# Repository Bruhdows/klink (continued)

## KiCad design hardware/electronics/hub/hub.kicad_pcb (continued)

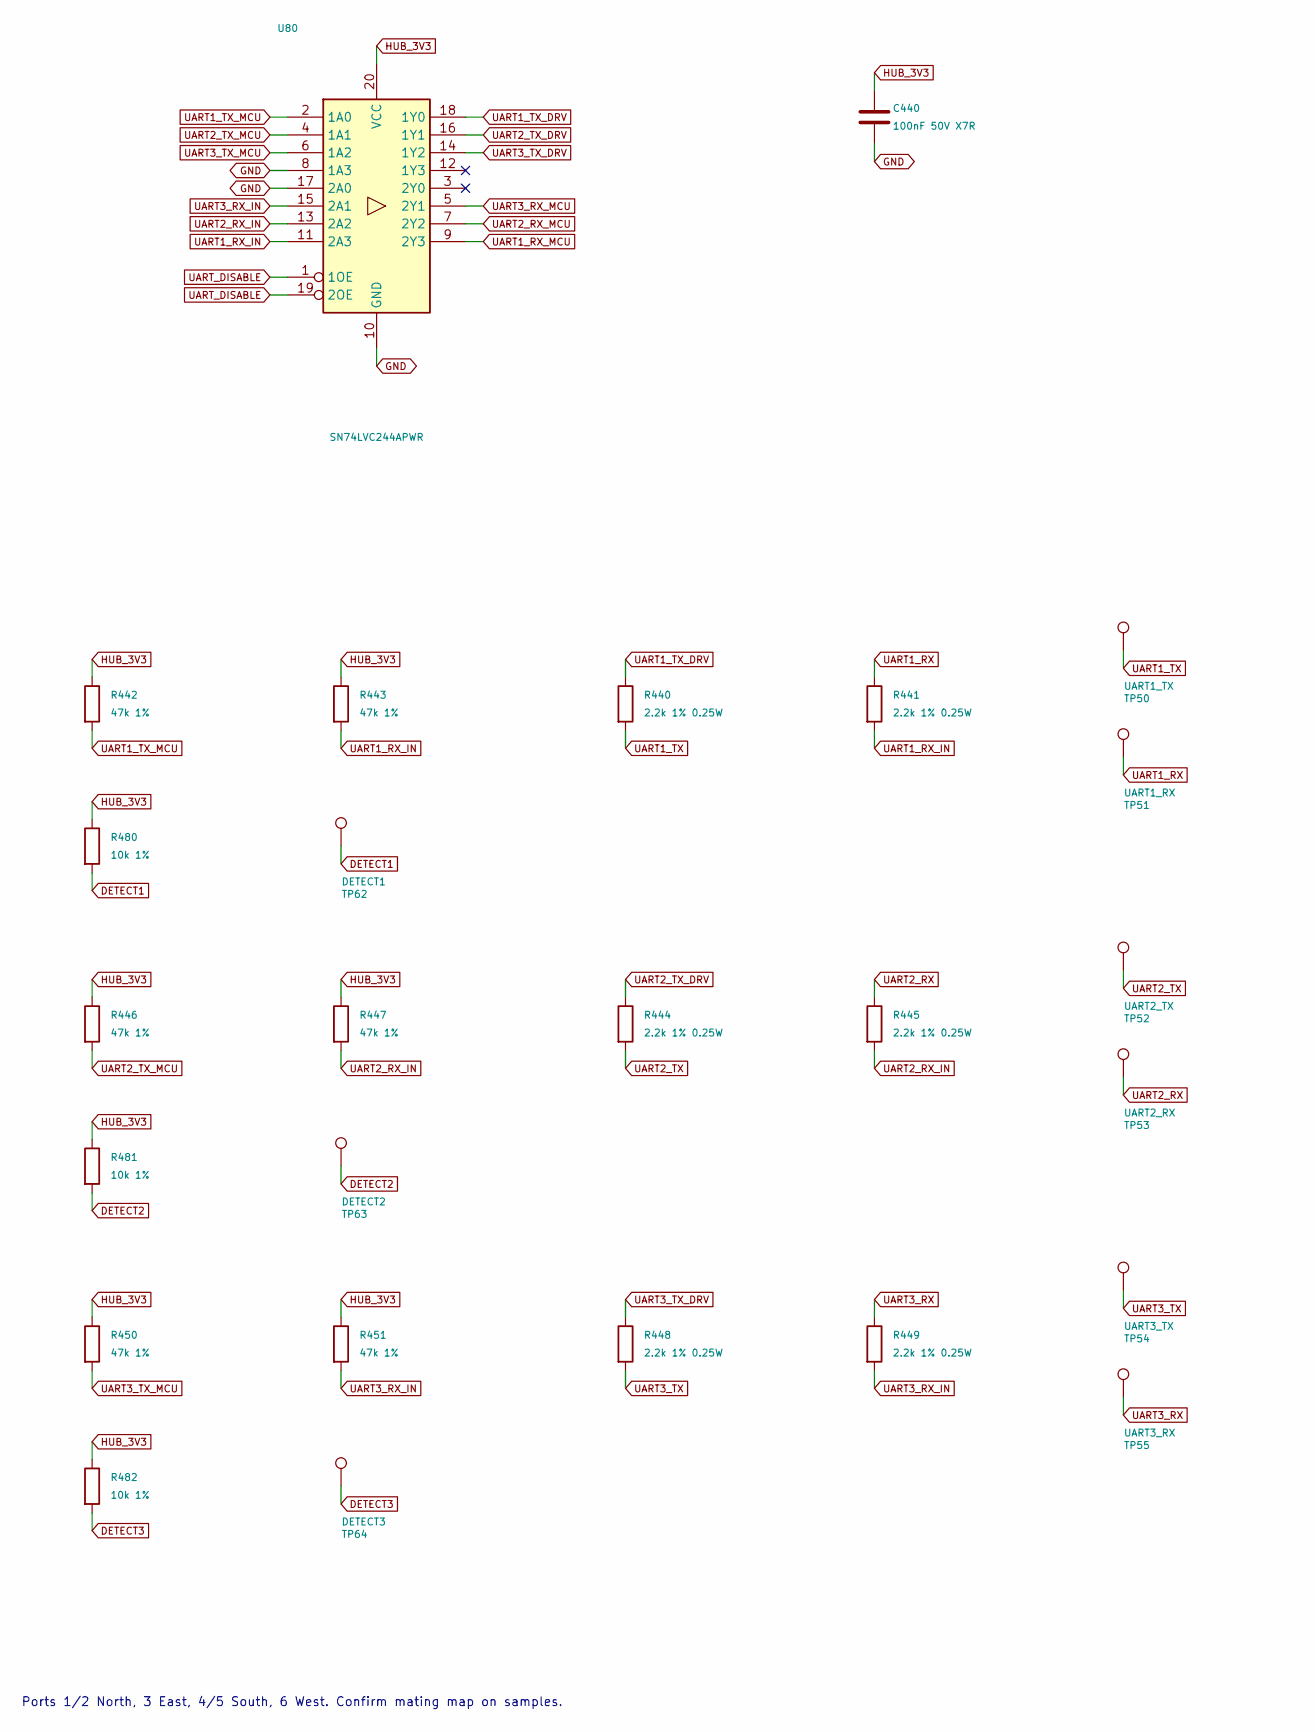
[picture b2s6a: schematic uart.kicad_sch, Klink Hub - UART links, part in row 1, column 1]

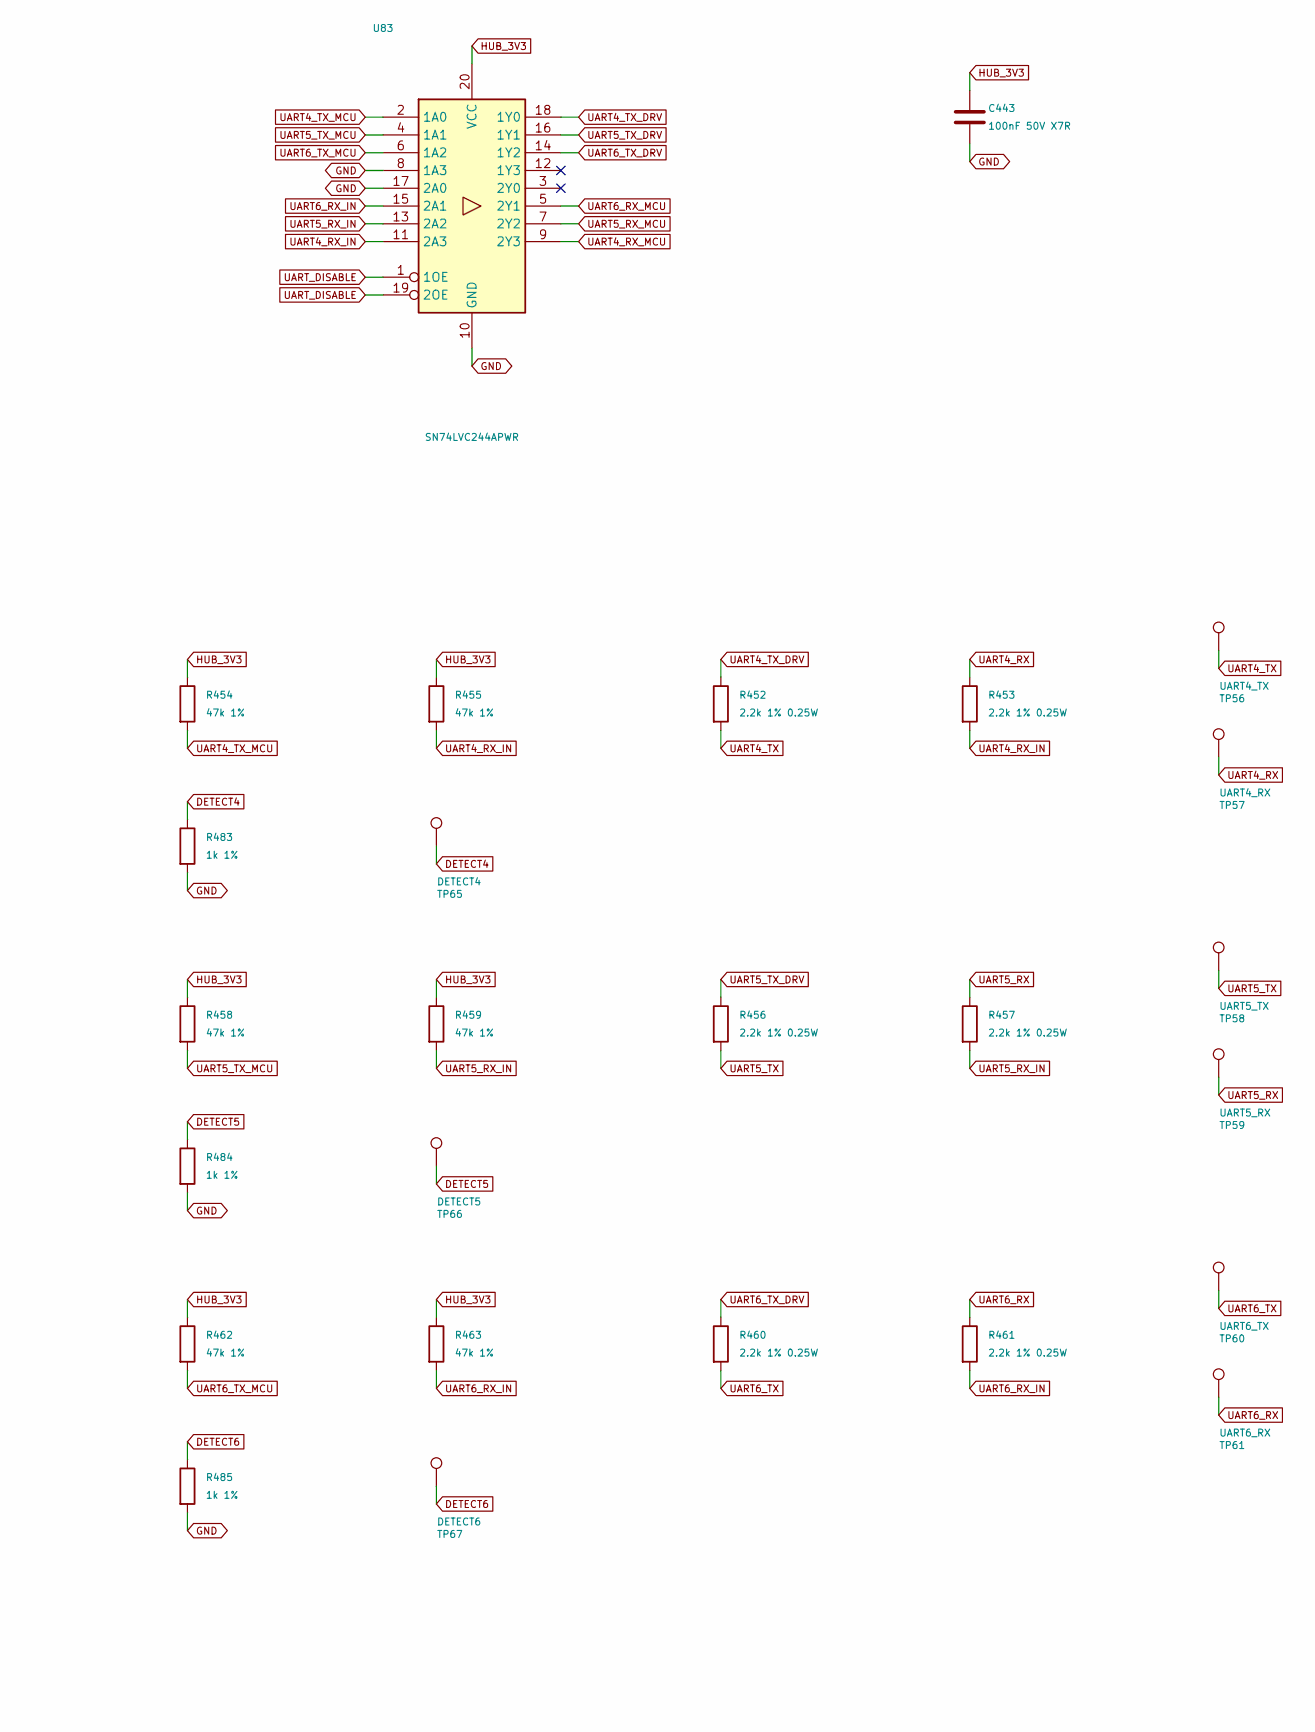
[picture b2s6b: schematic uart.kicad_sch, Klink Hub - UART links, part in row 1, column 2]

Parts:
C440, C443: 100nF 50V X7R; C_0805_2012Metric; MPN C2012X7R1H104K125AE
R440, R441, R444, R445, R448, R449, R452, R453, R456, R457, R460, R461: 2.2k 1% 0.25W; R_1206_3216Metric; MPN RC1206FR-072K2L
R442, R443, R446, R447, R450, R451, R454, R455, R458, R459, R462, R463: 47k 1%; R_0805_2012Metric; MPN RC0805FR-0747KL
R480, R481, R482: 10k 1%; R_0805_2012Metric; MPN RC0805FR-0710KL
R483, R484, R485: 1k 1%; R_0805_2012Metric; MPN RC0805FR-071KL
TP50: UART1_TX; TestPoint_Pad_D2.0mm
TP51: UART1_RX; TestPoint_Pad_D2.0mm
TP52: UART2_TX; TestPoint_Pad_D2.0mm
TP53: UART2_RX; TestPoint_Pad_D2.0mm
TP54: UART3_TX; TestPoint_Pad_D2.0mm
TP55: UART3_RX; TestPoint_Pad_D2.0mm
TP56: UART4_TX; TestPoint_Pad_D2.0mm
TP57: UART4_RX; TestPoint_Pad_D2.0mm
TP58: UART5_TX; TestPoint_Pad_D2.0mm
TP59: UART5_RX; TestPoint_Pad_D2.0mm
TP60: UART6_TX; TestPoint_Pad_D2.0mm
TP61: UART6_RX; TestPoint_Pad_D2.0mm
TP62: DETECT1; TestPoint_Pad_D2.0mm
TP63: DETECT2; TestPoint_Pad_D2.0mm
TP64: DETECT3; TestPoint_Pad_D2.0mm
TP65: DETECT4; TestPoint_Pad_D2.0mm
TP66: DETECT5; TestPoint_Pad_D2.0mm
TP67: DETECT6; TestPoint_Pad_D2.0mm
U80, U83: SN74LVC244APWR; TSSOP-20_4.4x6.5mm_P0.65mm; MPN SN74LVC244APWR

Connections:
DETECT1: R480.2, TP62.1; also elsewhere on the board
DETECT2: R481.2, TP63.1; also elsewhere on the board
DETECT3: R482.2, TP64.1; also elsewhere on the board
DETECT4: R483.1, TP65.1
DETECT5: R484.1, TP66.1
DETECT6: R485.1, TP67.1
GND: C440.2, C443.2, R483.2, R484.2, R485.2, U80.8 (1A3), U80.10 (GND), U80.17 (2A0), U83.8 (1A3), U83.10 (GND), U83.17 (2A0); also elsewhere on the board
HUB_3V3: C440.1, C443.1, R442.1, R443.1, R446.1, R447.1, R450.1, R451.1, R454.1, R455.1, R458.1, R459.1, R462.1, R463.1, R480.1, R481.1, R482.1, U80.20 (VCC), U83.20 (VCC); also elsewhere on the board
UART1_RX: R441.1, TP51.1
UART1_RX_IN: R441.2, R443.2, U80.11 (2A3)
UART1_RX_MCU: U80.9 (2Y3); also elsewhere on the board
UART1_TX: R440.2, TP50.1
UART1_TX_DRV: R440.1, U80.18 (1Y0)
UART1_TX_MCU: R442.2, U80.2 (1A0); also elsewhere on the board
UART2_RX: R445.1, TP53.1
UART2_RX_IN: R445.2, R447.2, U80.13 (2A2)
UART2_RX_MCU: U80.7 (2Y2); also elsewhere on the board
UART2_TX: R444.2, TP52.1
UART2_TX_DRV: R444.1, U80.16 (1Y1)
UART2_TX_MCU: R446.2, U80.4 (1A1); also elsewhere on the board
UART3_RX: R449.1, TP55.1
UART3_RX_IN: R449.2, R451.2, U80.15 (2A1)
UART3_RX_MCU: U80.5 (2Y1); also elsewhere on the board
UART3_TX: R448.2, TP54.1
UART3_TX_DRV: R448.1, U80.14 (1Y2)
UART3_TX_MCU: R450.2, U80.6 (1A2); also elsewhere on the board
UART4_RX: R453.1, TP57.1
UART4_RX_IN: R453.2, R455.2, U83.11 (2A3)
UART4_RX_MCU: U83.9 (2Y3); also elsewhere on the board
UART4_TX: R452.2, TP56.1
UART4_TX_DRV: R452.1, U83.18 (1Y0)
UART4_TX_MCU: R454.2, U83.2 (1A0); also elsewhere on the board
UART5_RX: R457.1, TP59.1
UART5_RX_IN: R457.2, R459.2, U83.13 (2A2)
UART5_RX_MCU: U83.7 (2Y2); also elsewhere on the board
UART5_TX: R456.2, TP58.1
UART5_TX_DRV: R456.1, U83.16 (1Y1)
UART5_TX_MCU: R458.2, U83.4 (1A1); also elsewhere on the board
UART6_RX: R461.1, TP61.1
UART6_RX_IN: R461.2, R463.2, U83.15 (2A1)
UART6_RX_MCU: U83.5 (2Y1); also elsewhere on the board
UART6_TX: R460.2, TP60.1
UART6_TX_DRV: R460.1, U83.14 (1Y2)
UART6_TX_MCU: R462.2, U83.6 (1A2); also elsewhere on the board
UART_DISABLE: U80.1 (1OE), U80.19 (2OE), U83.1 (1OE), U83.19 (2OE); also elsewhere on the board

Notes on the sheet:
Ports 1/2 North, 3 East, 4/5 South, 6 West. Confirm mating map on samples.

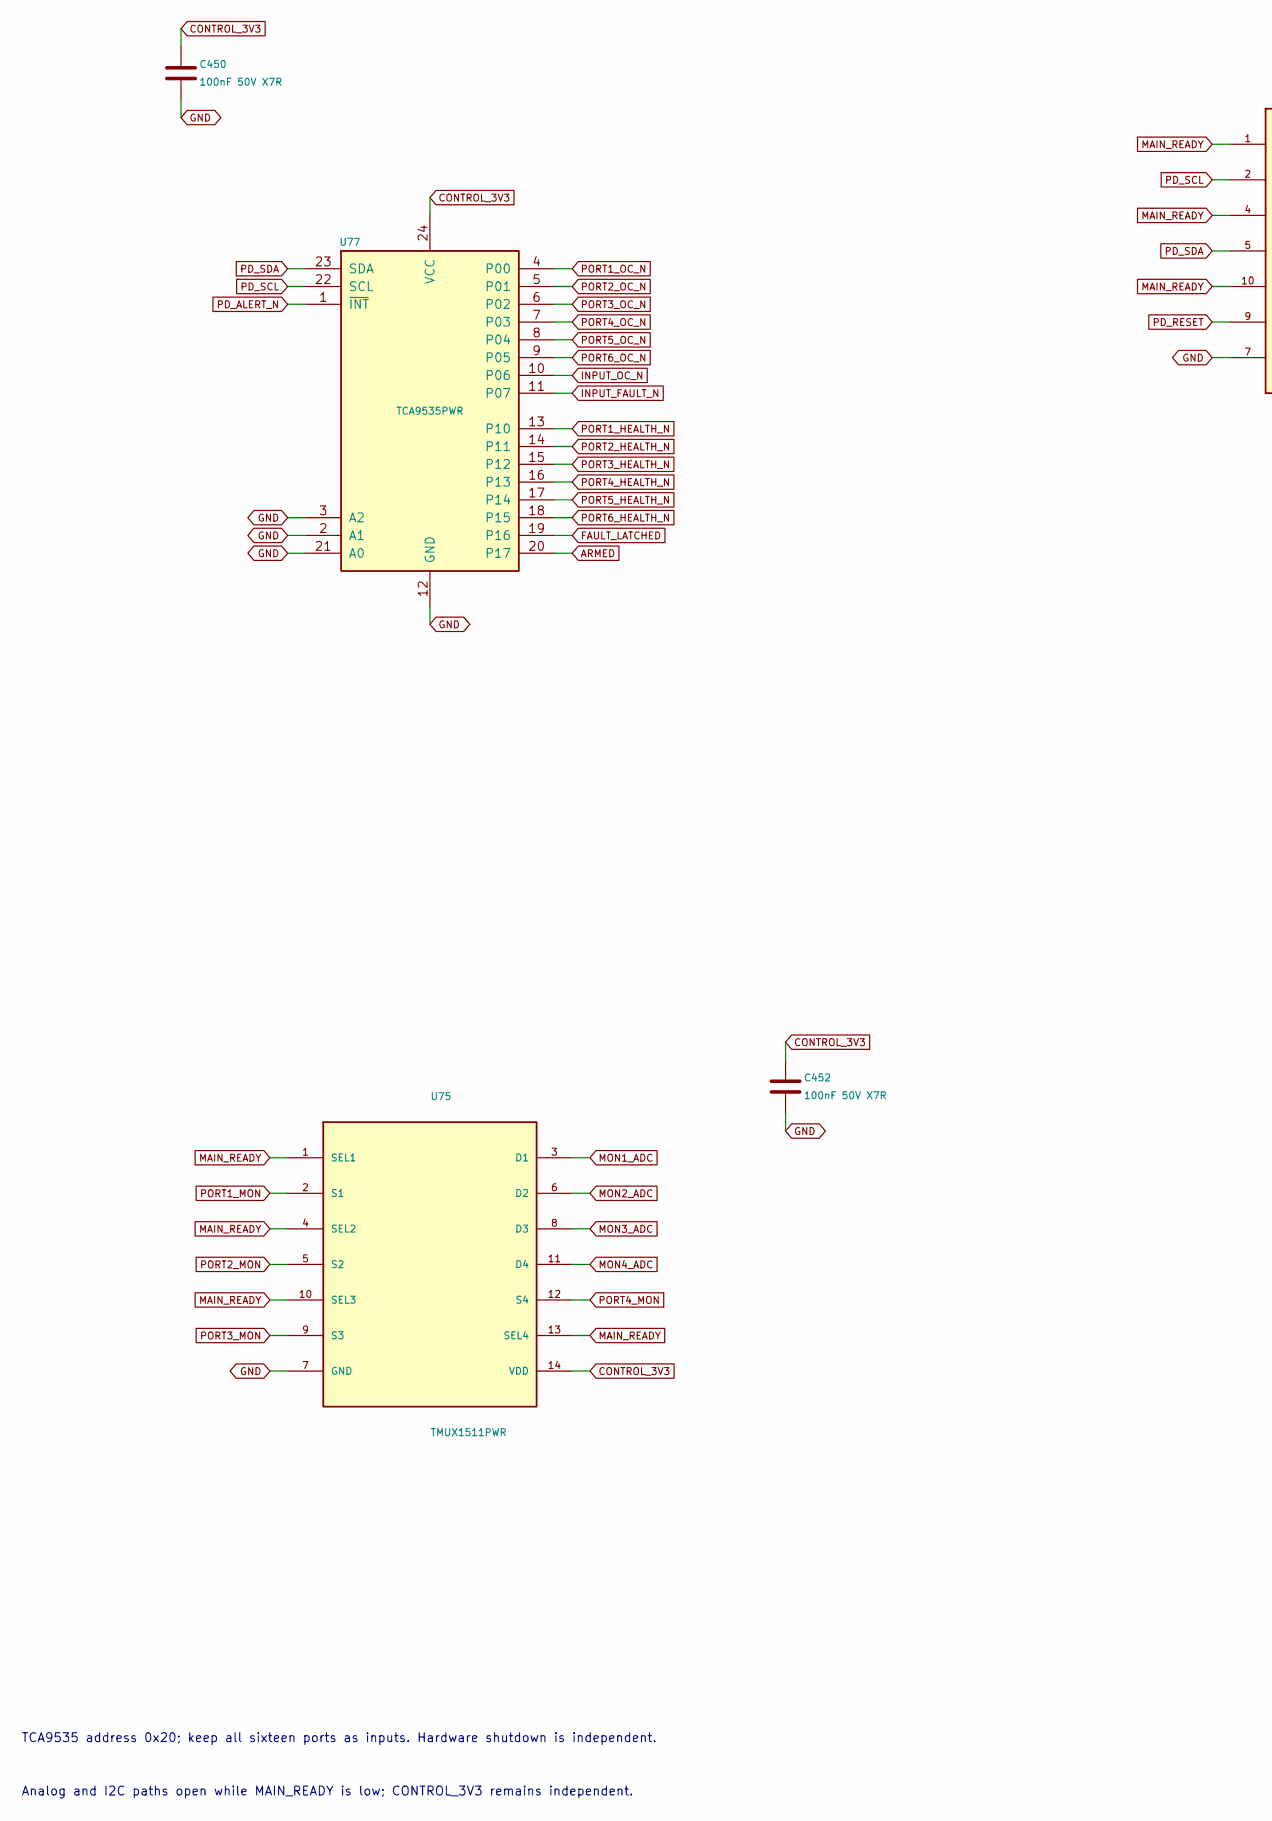
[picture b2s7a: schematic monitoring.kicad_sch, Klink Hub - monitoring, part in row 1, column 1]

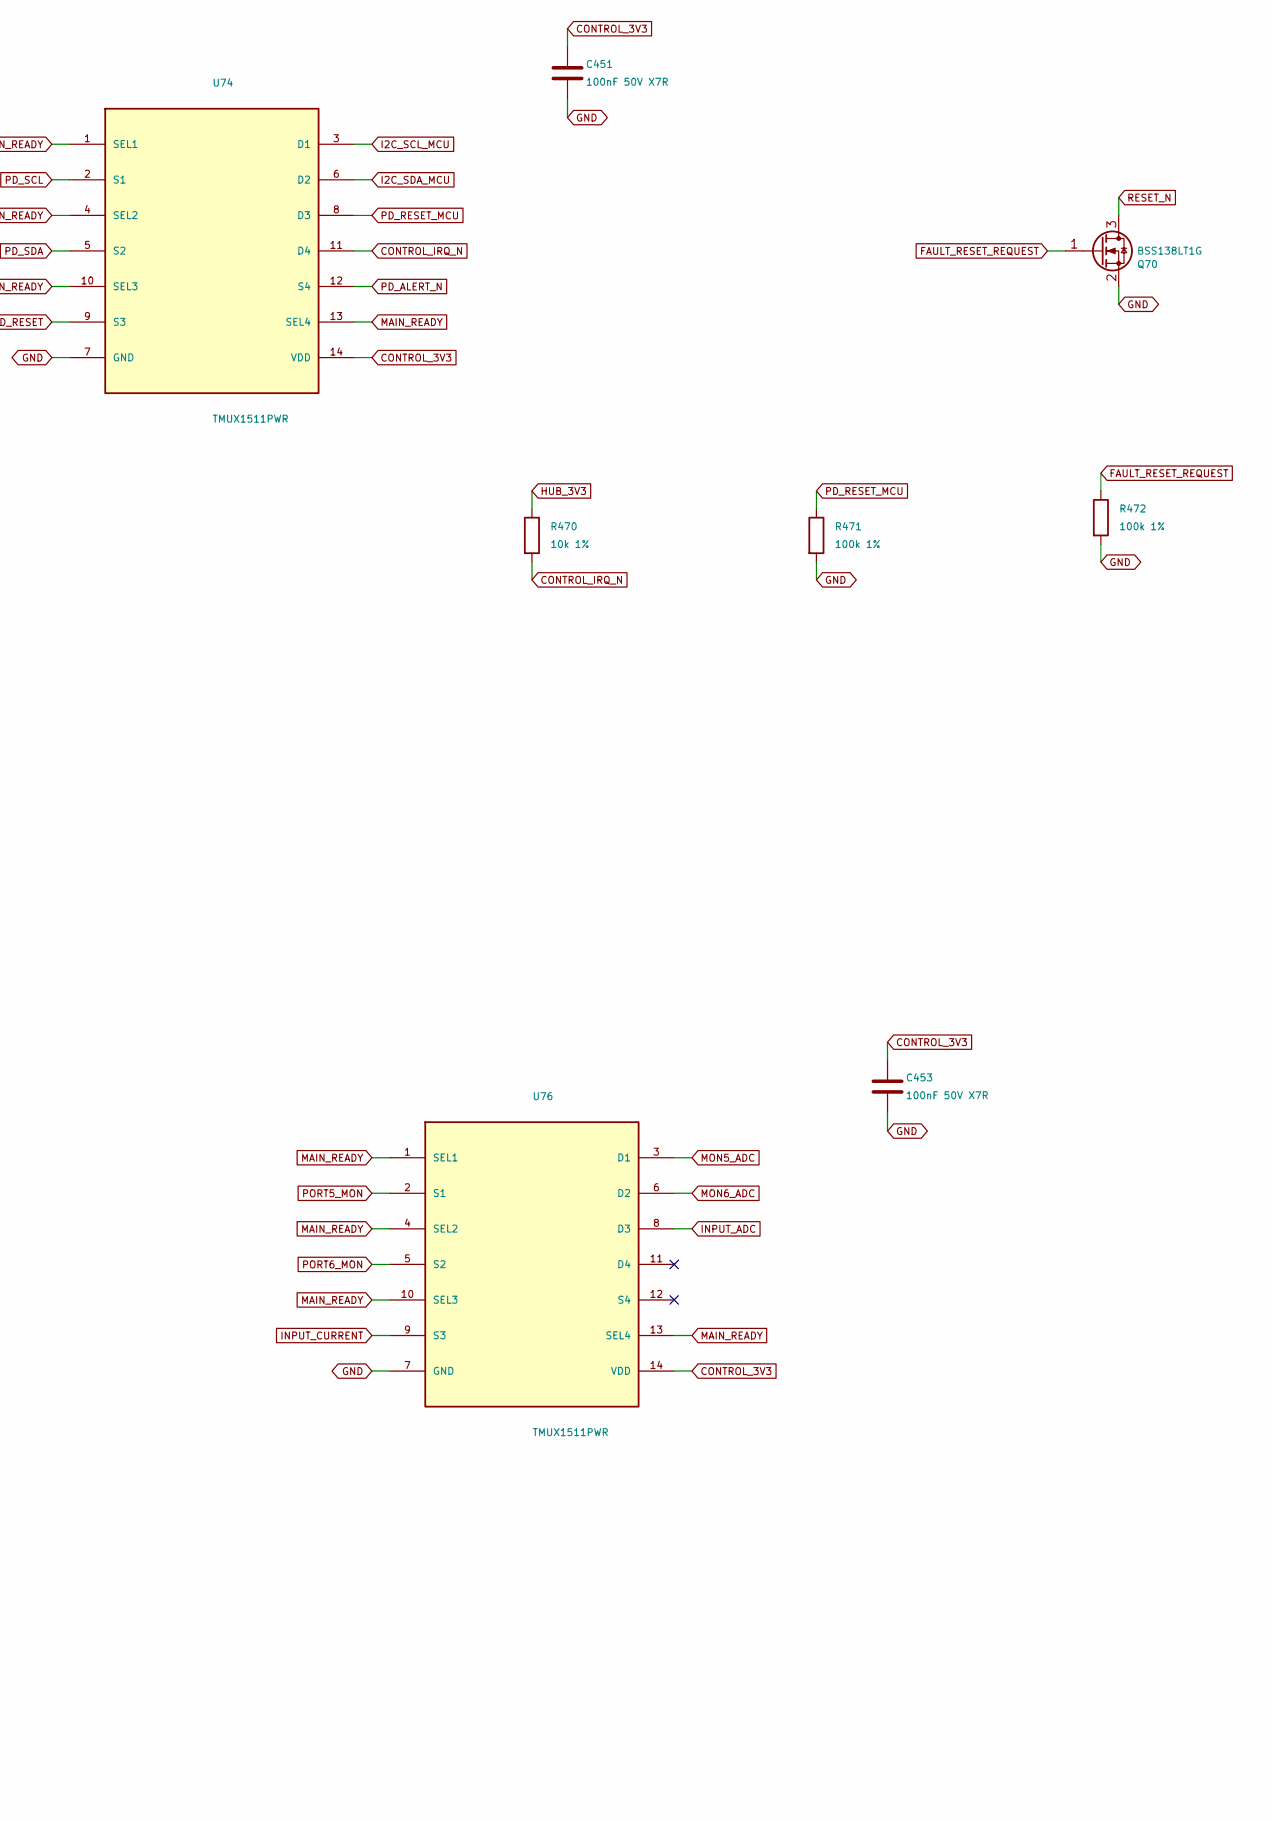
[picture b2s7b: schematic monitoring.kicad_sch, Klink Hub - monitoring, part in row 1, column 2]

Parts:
C450, C451, C452, C453: 100nF 50V X7R; C_0805_2012Metric; MPN C2012X7R1H104K125AE
Q70: BSS138LT1G; SOT-23; MPN BSS138LT1G
R470: 10k 1%; R_0805_2012Metric; MPN RC0805FR-0710KL
R471, R472: 100k 1%; R_0805_2012Metric; MPN RC0805FR-07100KL
U74, U75, U76: TMUX1511PWR; TSSOP-14_4.4x5mm_P0.65mm; MPN TMUX1511PWR
U77: TCA9535PWR; TSSOP-24_4.4x7.8mm_P0.65mm; MPN TCA9535PWR

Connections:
ARMED: U77.20 (P17); also elsewhere on the board
CONTROL_3V3: C450.1, C451.1, C452.1, C453.1, U74.14 (VDD), U75.14 (VDD), U76.14 (VDD), U77.24 (VCC); also elsewhere on the board
CONTROL_IRQ_N: R470.2, U74.11 (D4); also elsewhere on the board
FAULT_LATCHED: U77.19 (P16); also elsewhere on the board
FAULT_RESET_REQUEST: Q70.1 (G), R472.1; also elsewhere on the board
GND: C450.2, C451.2, C452.2, C453.2, Q70.2 (S), R471.2, R472.2, U74.7 (GND), U75.7 (GND), U76.7 (GND), U77.2 (A1), U77.3 (A2), U77.12 (GND), U77.21 (A0); also elsewhere on the board
HUB_3V3: R470.1; also elsewhere on the board
I2C_SCL_MCU: U74.3 (D1); also elsewhere on the board
I2C_SDA_MCU: U74.6 (D2); also elsewhere on the board
INPUT_ADC: U76.8 (D3); also elsewhere on the board
INPUT_CURRENT: U76.9 (S3); also elsewhere on the board
INPUT_FAULT_N: U77.11 (P07); also elsewhere on the board
INPUT_OC_N: U77.10 (P06); also elsewhere on the board
MAIN_READY: U74.1 (SEL1), U74.4 (SEL2), U74.10 (SEL3), U74.13 (SEL4), U75.1 (SEL1), U75.4 (SEL2), U75.10 (SEL3), U75.13 (SEL4), U76.1 (SEL1), U76.4 (SEL2), U76.10 (SEL3), U76.13 (SEL4); also elsewhere on the board
MON1_ADC: U75.3 (D1); also elsewhere on the board
MON2_ADC: U75.6 (D2); also elsewhere on the board
MON3_ADC: U75.8 (D3); also elsewhere on the board
MON4_ADC: U75.11 (D4); also elsewhere on the board
MON5_ADC: U76.3 (D1); also elsewhere on the board
MON6_ADC: U76.6 (D2); also elsewhere on the board
PD_ALERT_N: U74.12 (S4), U77.1 (~INT); also elsewhere on the board
PD_RESET: U74.9 (S3); also elsewhere on the board
PD_RESET_MCU: R471.1, U74.8 (D3); also elsewhere on the board
PD_SCL: U74.2 (S1), U77.22 (SCL); also elsewhere on the board
PD_SDA: U74.5 (S2), U77.23 (SDA); also elsewhere on the board
PORT1_HEALTH_N: U77.13 (P10); also elsewhere on the board
PORT1_MON: U75.2 (S1); also elsewhere on the board
PORT1_OC_N: U77.4 (P00); also elsewhere on the board
PORT2_HEALTH_N: U77.14 (P11); also elsewhere on the board
PORT2_MON: U75.5 (S2); also elsewhere on the board
PORT2_OC_N: U77.5 (P01); also elsewhere on the board
PORT3_HEALTH_N: U77.15 (P12); also elsewhere on the board
PORT3_MON: U75.9 (S3); also elsewhere on the board
PORT3_OC_N: U77.6 (P02); also elsewhere on the board
PORT4_HEALTH_N: U77.16 (P13); also elsewhere on the board
PORT4_MON: U75.12 (S4); also elsewhere on the board
PORT4_OC_N: U77.7 (P03); also elsewhere on the board
PORT5_HEALTH_N: U77.17 (P14); also elsewhere on the board
PORT5_MON: U76.2 (S1); also elsewhere on the board
PORT5_OC_N: U77.8 (P04); also elsewhere on the board
PORT6_HEALTH_N: U77.18 (P15); also elsewhere on the board
PORT6_MON: U76.5 (S2); also elsewhere on the board
PORT6_OC_N: U77.9 (P05); also elsewhere on the board
RESET_N: Q70.3 (D); also elsewhere on the board

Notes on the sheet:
TCA9535 address 0x20; keep all sixteen ports as inputs. Hardware shutdown is independent.
Analog and I2C paths open while MAIN_READY is low; CONTROL_3V3 remains independent.

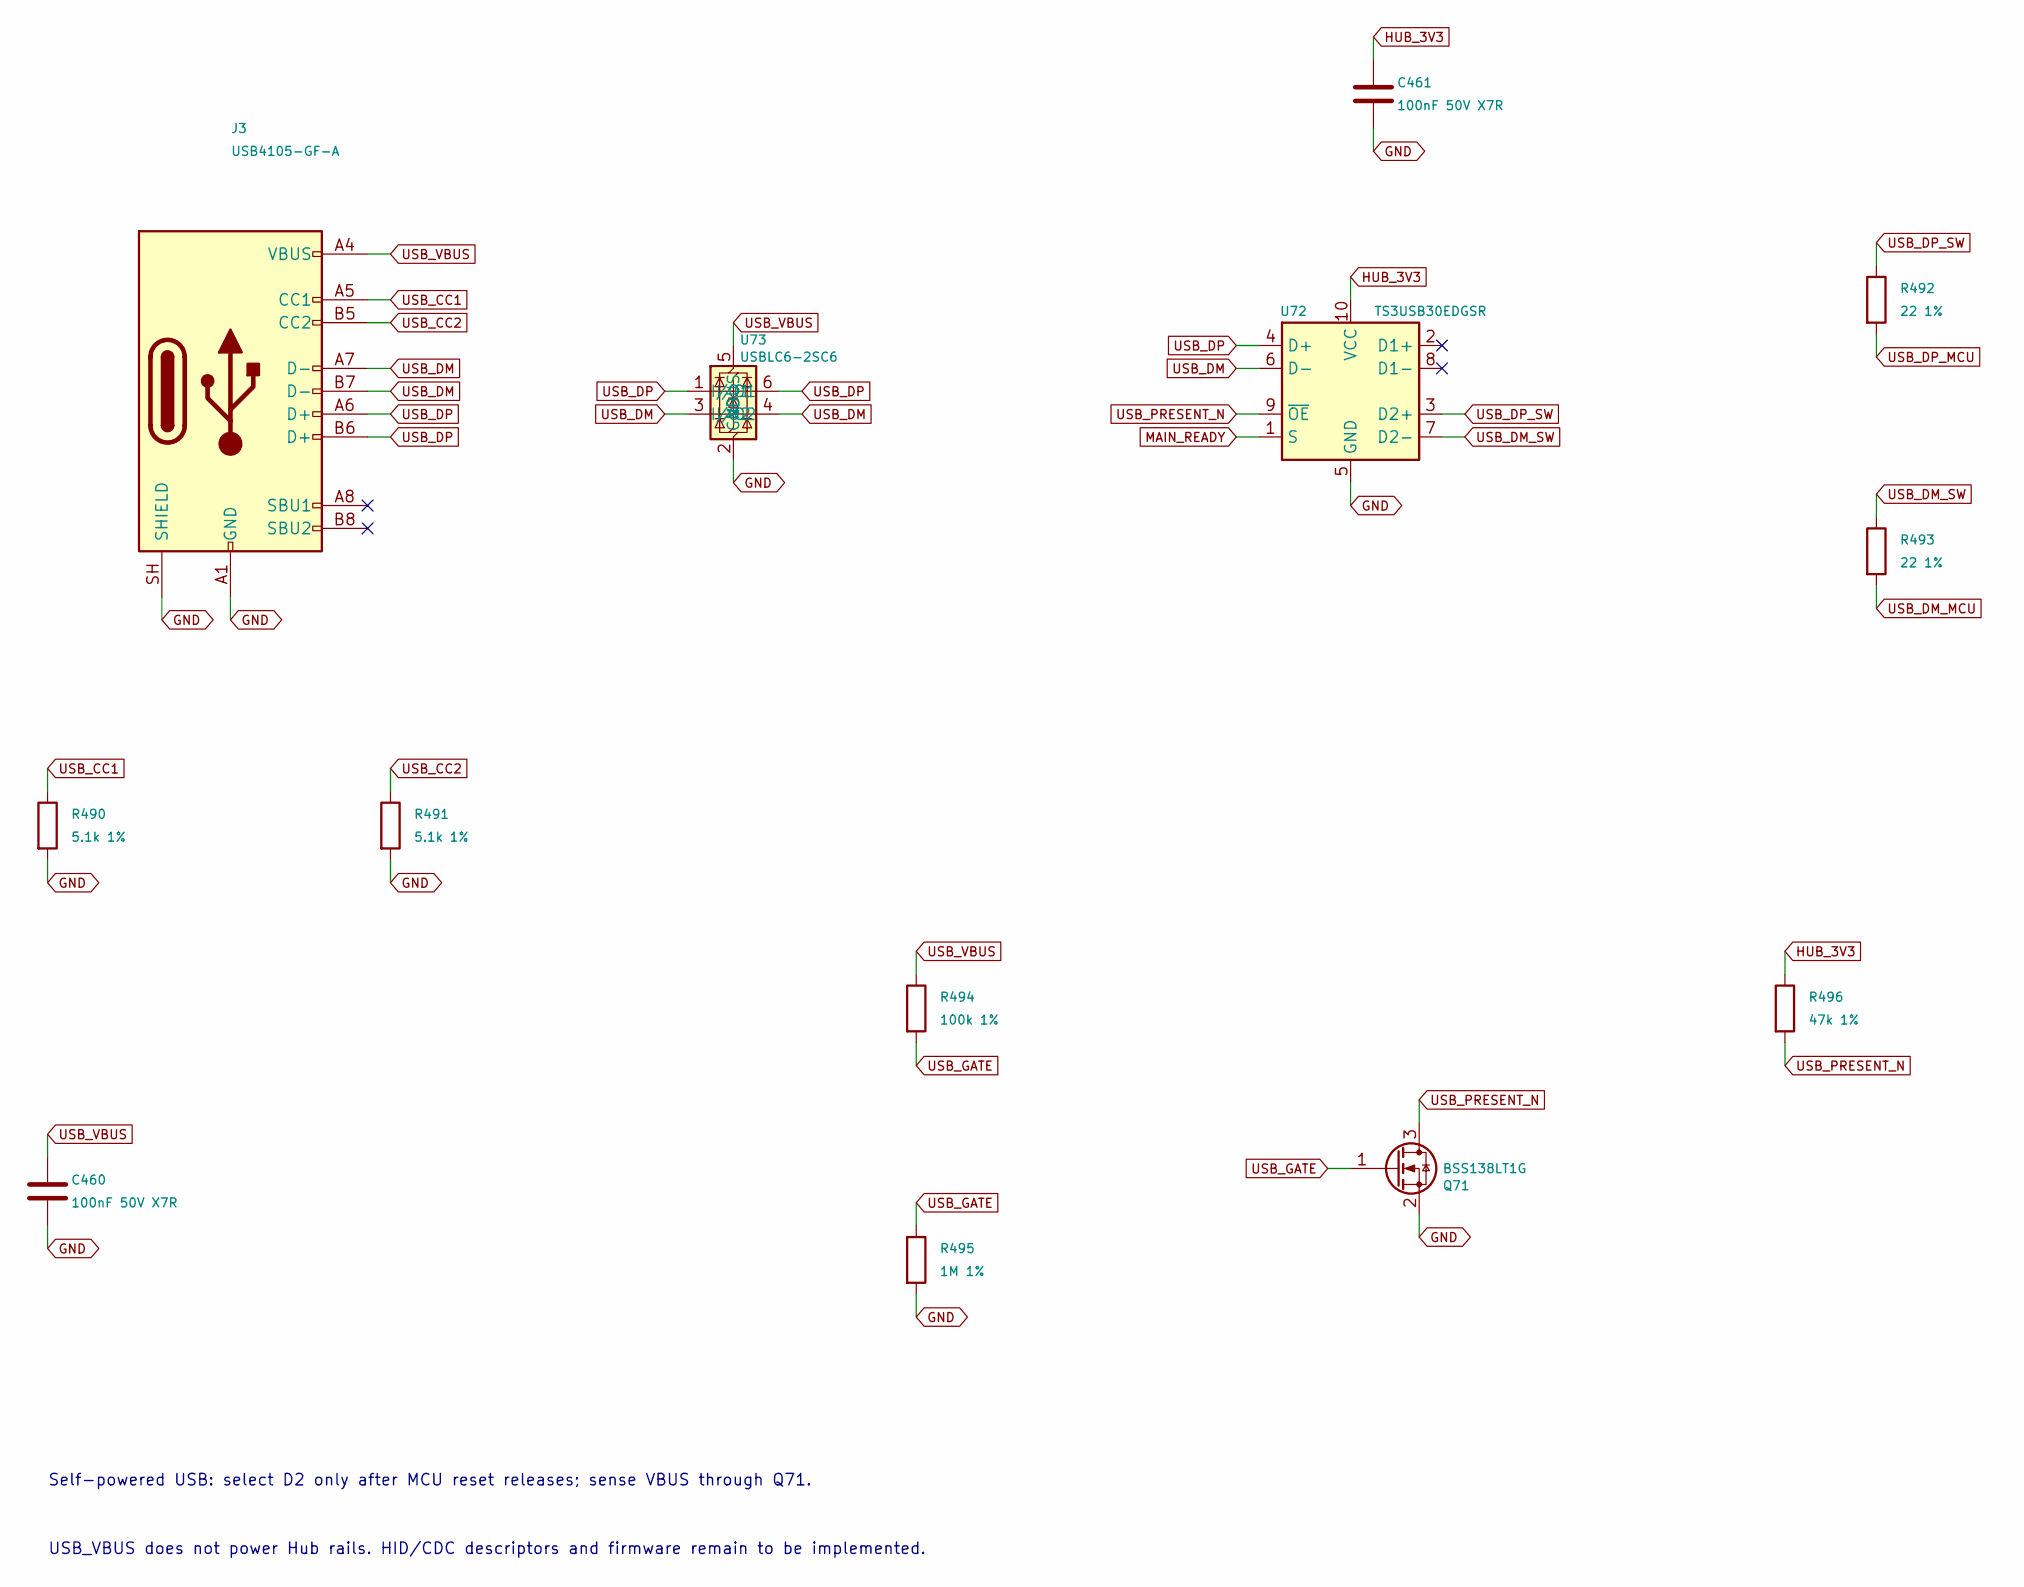
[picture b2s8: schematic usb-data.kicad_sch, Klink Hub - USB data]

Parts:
C460, C461: 100nF 50V X7R; C_0805_2012Metric; MPN C2012X7R1H104K125AE
J3: USB4105-GF-A; USB_C_Receptacle_GCT_USB4105_RoundedGround; MPN USB4105-GF-A
Q71: BSS138LT1G; SOT-23; MPN BSS138LT1G
R490, R491: 5.1k 1%; R_0805_2012Metric; MPN RC0805FR-075K1L
R492, R493: 22 1%; R_0805_2012Metric; MPN RC0805FR-0722RL
R494: 100k 1%; R_0805_2012Metric; MPN RC0805FR-07100KL
R495: 1M 1%; R_0805_2012Metric; MPN RC0805FR-071ML
R496: 47k 1%; R_0805_2012Metric; MPN RC0805FR-0747KL
U72: TS3USB30EDGSR; TSSOP-10_3x3mm_P0.5mm; MPN TS3USB30EDGSR
U73: USBLC6-2SC6; SOT-23-6; MPN USBLC6-2SC6

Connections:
GND: C460.2, C461.2, J3.A1 (GND), J3.A12 (GND), J3.B1 (GND), J3.B12 (GND), J3.SH (SHIELD), Q71.2 (S), R490.2, R491.2, R495.2, U72.5 (GND), U73.2 (GND); also elsewhere on the board
HUB_3V3: C461.1, R496.1, U72.10 (VCC); also elsewhere on the board
MAIN_READY: U72.1 (S); also elsewhere on the board
USB_CC1: J3.A5 (CC1), R490.1
USB_CC2: J3.B5 (CC2), R491.1
USB_DM: J3.A7 (D-), J3.B7 (D-), U72.6 (D-), U73.3 (I/O2), U73.4 (I/O2)
USB_DM_MCU: R493.2; also elsewhere on the board
USB_DM_SW: R493.1, U72.7 (D2-)
USB_DP: J3.A6 (D+), J3.B6 (D+), U72.4 (D+), U73.1 (I/O1), U73.6 (I/O1)
USB_DP_MCU: R492.2; also elsewhere on the board
USB_DP_SW: R492.1, U72.3 (D2+)
USB_GATE: Q71.1 (G), R494.2, R495.1
USB_PRESENT_N: Q71.3 (D), R496.2, U72.9 (~OE); also elsewhere on the board
USB_VBUS: C460.1, J3.A4 (VBUS), J3.A9 (VBUS), J3.B4 (VBUS), J3.B9 (VBUS), R494.1, U73.5 (VBUS)

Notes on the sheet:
Self-powered USB: select D2 only after MCU reset releases; sense VBUS through Q71.
USB_VBUS does not power Hub rails. HID/CDC descriptors and firmware remain to be implemented.
